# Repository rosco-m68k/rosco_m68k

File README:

# Motorola 68k single-board computer

This repository holds design files, firmware and software for my m68k 
single-board computer, AKA the Rosco_m68k.

You can find the project along with some logs about its development
on Hackaday: https://hackaday.io/project/164305-yet-another-m68k-homebrew

All released under the MIT licence. See LICENSE for details.

## Current design

Currently, the design for the system is:

* MC68010P10 at 8MHz, /DTACK grounded
* 16KB IO Space (0xF80000 - 0xFEFFFF)
* 16KB ROM (at 0xFC0000)
* 1MB RAM (0x0 - 0xFFFFF)
* TTL-based address decoding

In terms of software:

* Simple code in ROM to do various tests etc.
* Built with GCC and VASM

## Next steps

* Integrate MC68901 MFP
** This will provide timers, and a UART we can use to hook up a terminal. It also has some GPIOs and does interrupt handling (I already have the IC).
* Graphics - I'm thinking maybe Yamaha V9958 (assuming I can get hold of one)
** I would have liked to have used a Denise, but that would probably also require a (non-breadboard-friendly) Agnus.
** The datasheet and manual for the Denise probably aren't as easy to come by or complete, so there'd be more reverse-engineering.
* OS - Once the timers are available and I have some I/O capability, I want to build out the OS.
** Microkernel architecture (Similar in principle to Exec)
** Preemptive multitasking
** External storage (probably CF or SD in the first instance, though SD would require level shifting).

## Ideas for future enhancement

### Minimal memory protection

Extend address decoder to disallow access to certain locations based on 68k function pins.
E.g. in user mode:

	* Disallow ROM
	* Disallow IO
	* Disallow xKB at bottom of RAM (ExVecs and kernel heap)

The last one would make null dereferences generate a bus error.

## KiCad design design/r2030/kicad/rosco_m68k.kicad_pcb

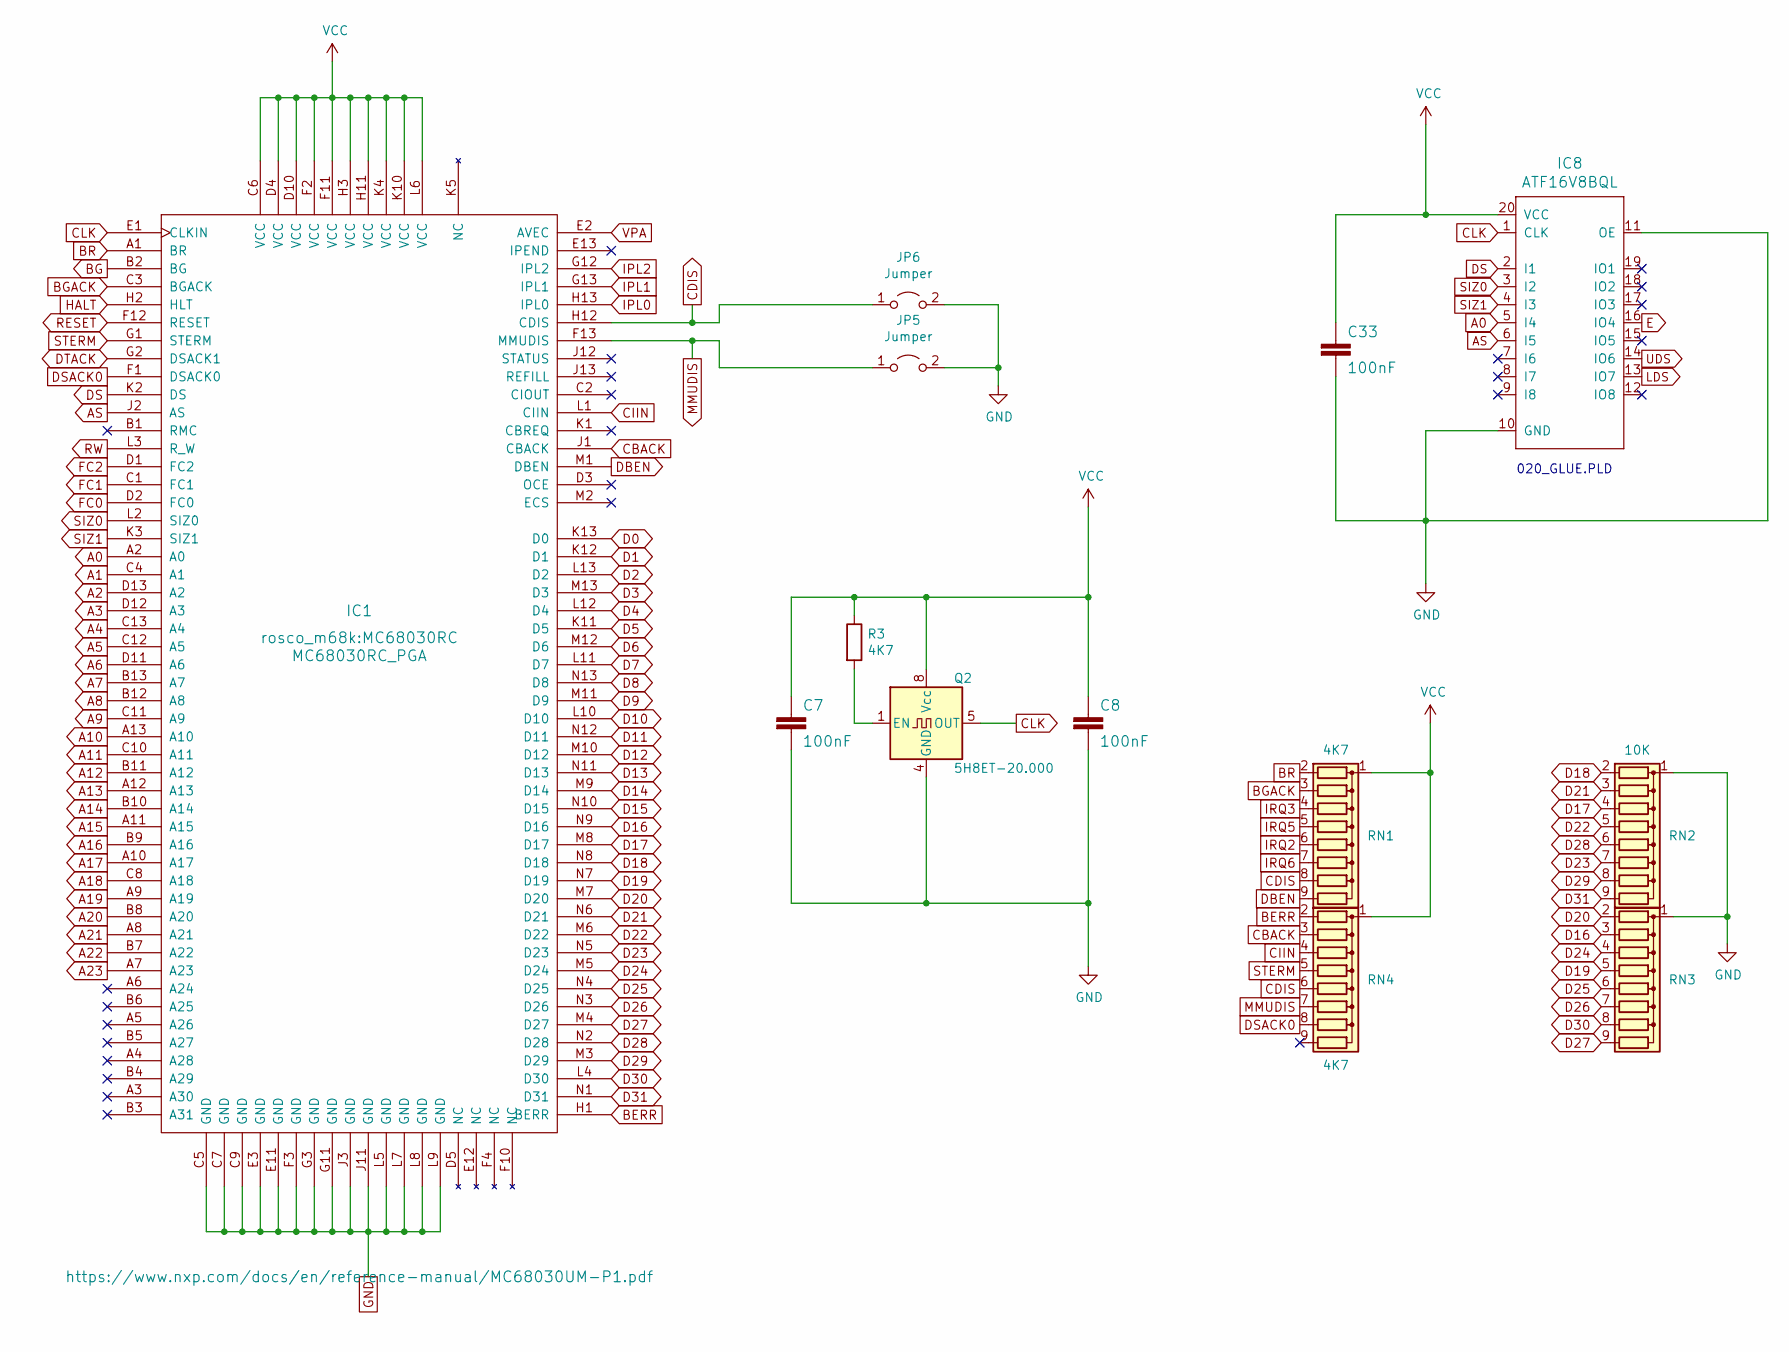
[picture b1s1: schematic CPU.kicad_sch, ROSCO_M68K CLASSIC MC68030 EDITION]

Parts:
C7, C8, C33: 100nF; C2.5-3
IC1: MC68030RC_PGA; MC68030RC
IC8: ATF16V8BQL; DIL20
JP5, JP6: Jumper; 1X02
Q2: 5H8ET-20.000; Oscillator_DIP-8
R3: 4K7; 0207_10
RN1, RN4: 4K7; R_Array_SIP9
RN2: 10K; R_Array_SIP9
RN3: R_Network08; R_Array_SIP9

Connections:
A0: IC1.A2 (A0), IC8.5 (I4)
A1: IC1.C4 (A1); also elsewhere on the board
A2: IC1.D13 (A2); also elsewhere on the board
A3: IC1.D12 (A3); also elsewhere on the board
A4: IC1.C13 (A4); also elsewhere on the board
A5: IC1.C12 (A5); also elsewhere on the board
A6: IC1.D11 (A6); also elsewhere on the board
A7: IC1.B13 (A7); also elsewhere on the board
A8: IC1.B12 (A8); also elsewhere on the board
A9: IC1.C11 (A9); also elsewhere on the board
A10: IC1.A13 (A10); also elsewhere on the board
A11: IC1.C10 (A11); also elsewhere on the board
A12: IC1.B11 (A12); also elsewhere on the board
A13: IC1.A12 (A13); also elsewhere on the board
A14: IC1.B10 (A14); also elsewhere on the board
A15: IC1.A11 (A15); also elsewhere on the board
A16: IC1.B9 (A16); also elsewhere on the board
A17: IC1.A10 (A17); also elsewhere on the board
A18: IC1.C8 (A18); also elsewhere on the board
A19: IC1.A9 (A19); also elsewhere on the board
A20: IC1.B8 (A20); also elsewhere on the board
A21: IC1.A8 (A21); also elsewhere on the board
A22: IC1.B7 (A22); also elsewhere on the board
A23: IC1.A7 (A23); also elsewhere on the board
AS: IC1.J2 (AS), IC8.6 (I5); also elsewhere on the board
BERR: IC1.H1 (BERR), RN4.2 (R1); also elsewhere on the board
BG: IC1.B2 (BG); also elsewhere on the board
BGACK: IC1.C3 (BGACK), RN1.3 (R2); also elsewhere on the board
BR: IC1.A1 (BR), RN1.2 (R1); also elsewhere on the board
CBACK: IC1.J1 (CBACK), RN4.3 (R2)
CDIS: IC1.H12 (CDIS), JP6.1 (A), RN1.8 (R7), RN4.6 (R5)
CIIN: IC1.L1 (CIIN), RN4.4 (R3)
CLK: IC1.E1 (CLKIN), IC8.1 (CLK), Q2.5 (OUT); also elsewhere on the board
D0: IC1.K13 (D0); also elsewhere on the board
D1: IC1.K12 (D1); also elsewhere on the board
D2: IC1.L13 (D2); also elsewhere on the board
D3: IC1.M13 (D3); also elsewhere on the board
D4: IC1.L12 (D4); also elsewhere on the board
D5: IC1.K11 (D5); also elsewhere on the board
D6: IC1.M12 (D6); also elsewhere on the board
D7: IC1.L11 (D7); also elsewhere on the board
D8: IC1.N13 (D8); also elsewhere on the board
D9: IC1.M11 (D9); also elsewhere on the board
D10: IC1.L10 (D10); also elsewhere on the board
D11: IC1.N12 (D11); also elsewhere on the board
D12: IC1.M10 (D12); also elsewhere on the board
D13: IC1.N11 (D13); also elsewhere on the board
D14: IC1.M9 (D14); also elsewhere on the board
D15: IC1.N10 (D15); also elsewhere on the board
D16: IC1.N9 (D16), RN3.3 (R2)
D17: IC1.M8 (D17), RN2.4 (R3)
D18: IC1.N8 (D18), RN2.2 (R1)
D19: IC1.N7 (D19), RN3.5 (R4)
D20: IC1.M7 (D20), RN3.2 (R1)
D21: IC1.N6 (D21), RN2.3 (R2)
D22: IC1.M6 (D22), RN2.5 (R4)
D23: IC1.N5 (D23), RN2.7 (R6)
D24: IC1.M5 (D24), RN3.4 (R3)
D25: IC1.N4 (D25), RN3.6 (R5)
D26: IC1.N3 (D26), RN3.7 (R6)
D27: IC1.M4 (D27), RN3.9 (R8)
D28: IC1.N2 (D28), RN2.6 (R5)
D29: IC1.M3 (D29), RN2.8 (R7)
D30: IC1.L4 (D30), RN3.8 (R7)
D31: IC1.N1 (D31), RN2.9 (R8)
DBEN: IC1.M1 (DBEN), RN1.9 (R8)
DS: IC1.K2 (DS), IC8.2 (I1)
DSACK0: IC1.F1 (DSACK0), RN4.8 (R7)
DTACK: IC1.G2 (DSACK1); also elsewhere on the board
E: IC8.16 (IO4); also elsewhere on the board
FC0: IC1.D2 (FC0); also elsewhere on the board
FC1: IC1.C1 (FC1); also elsewhere on the board
FC2: IC1.D1 (FC2); also elsewhere on the board
GND: C7.2, C8.2, C33.2, IC1.C5 (GND), IC1.C7 (GND), IC1.C9 (GND), IC1.E3 (GND), IC1.E11 (GND), IC1.F3 (GND), IC1.G3 (GND), IC1.G11 (GND), IC1.J3 (GND), IC1.J11 (GND), IC1.L5 (GND), IC1.L7 (GND), IC1.L8 (GND), IC1.L9 (GND), IC8.10 (GND), IC8.11 (OE), JP5.2 (B), JP6.2 (B), Q2.4 (GND), RN2.1 (common), RN3.1 (common); also elsewhere on the board
HALT: IC1.H2 (HLT); also elsewhere on the board
IPL0: IC1.H13 (IPL0); also elsewhere on the board
IPL1: IC1.G13 (IPL1); also elsewhere on the board
IPL2: IC1.G12 (IPL2); also elsewhere on the board
IRQ2: RN1.6 (R5); also elsewhere on the board
IRQ3: RN1.4 (R3); also elsewhere on the board
IRQ5: RN1.5 (R4); also elsewhere on the board
IRQ6: RN1.7 (R6); also elsewhere on the board
LDS: IC8.13 (IO7); also elsewhere on the board
MMUDIS: IC1.F13 (MMUDIS), JP5.1 (A), RN4.7 (R6)
unnamed: Q2.1 (EN), R3.2
RESET: IC1.F12 (RESET); also elsewhere on the board
RW: IC1.L3 (R_W); also elsewhere on the board
SIZ0: IC1.L2 (SIZ0), IC8.3 (I2)
SIZ1: IC1.K3 (SIZ1), IC8.4 (I3)
STERM: IC1.G1 (STERM), RN4.5 (R4)
UDS: IC8.14 (IO6); also elsewhere on the board
VCC: C7.1, C8.1, C33.1, IC1.C6 (VCC), IC1.D4 (VCC), IC1.D10 (VCC), IC1.F2 (VCC), IC1.F11 (VCC), IC1.H3 (VCC), IC1.H11 (VCC), IC1.K4 (VCC), IC1.K10 (VCC), IC1.L6 (VCC), IC8.20 (VCC), Q2.8 (Vcc), R3.1, RN1.1 (common), RN4.1 (common); also elsewhere on the board
VPA: IC1.E2 (AVEC); also elsewhere on the board

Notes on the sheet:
020_GLUE.PLD

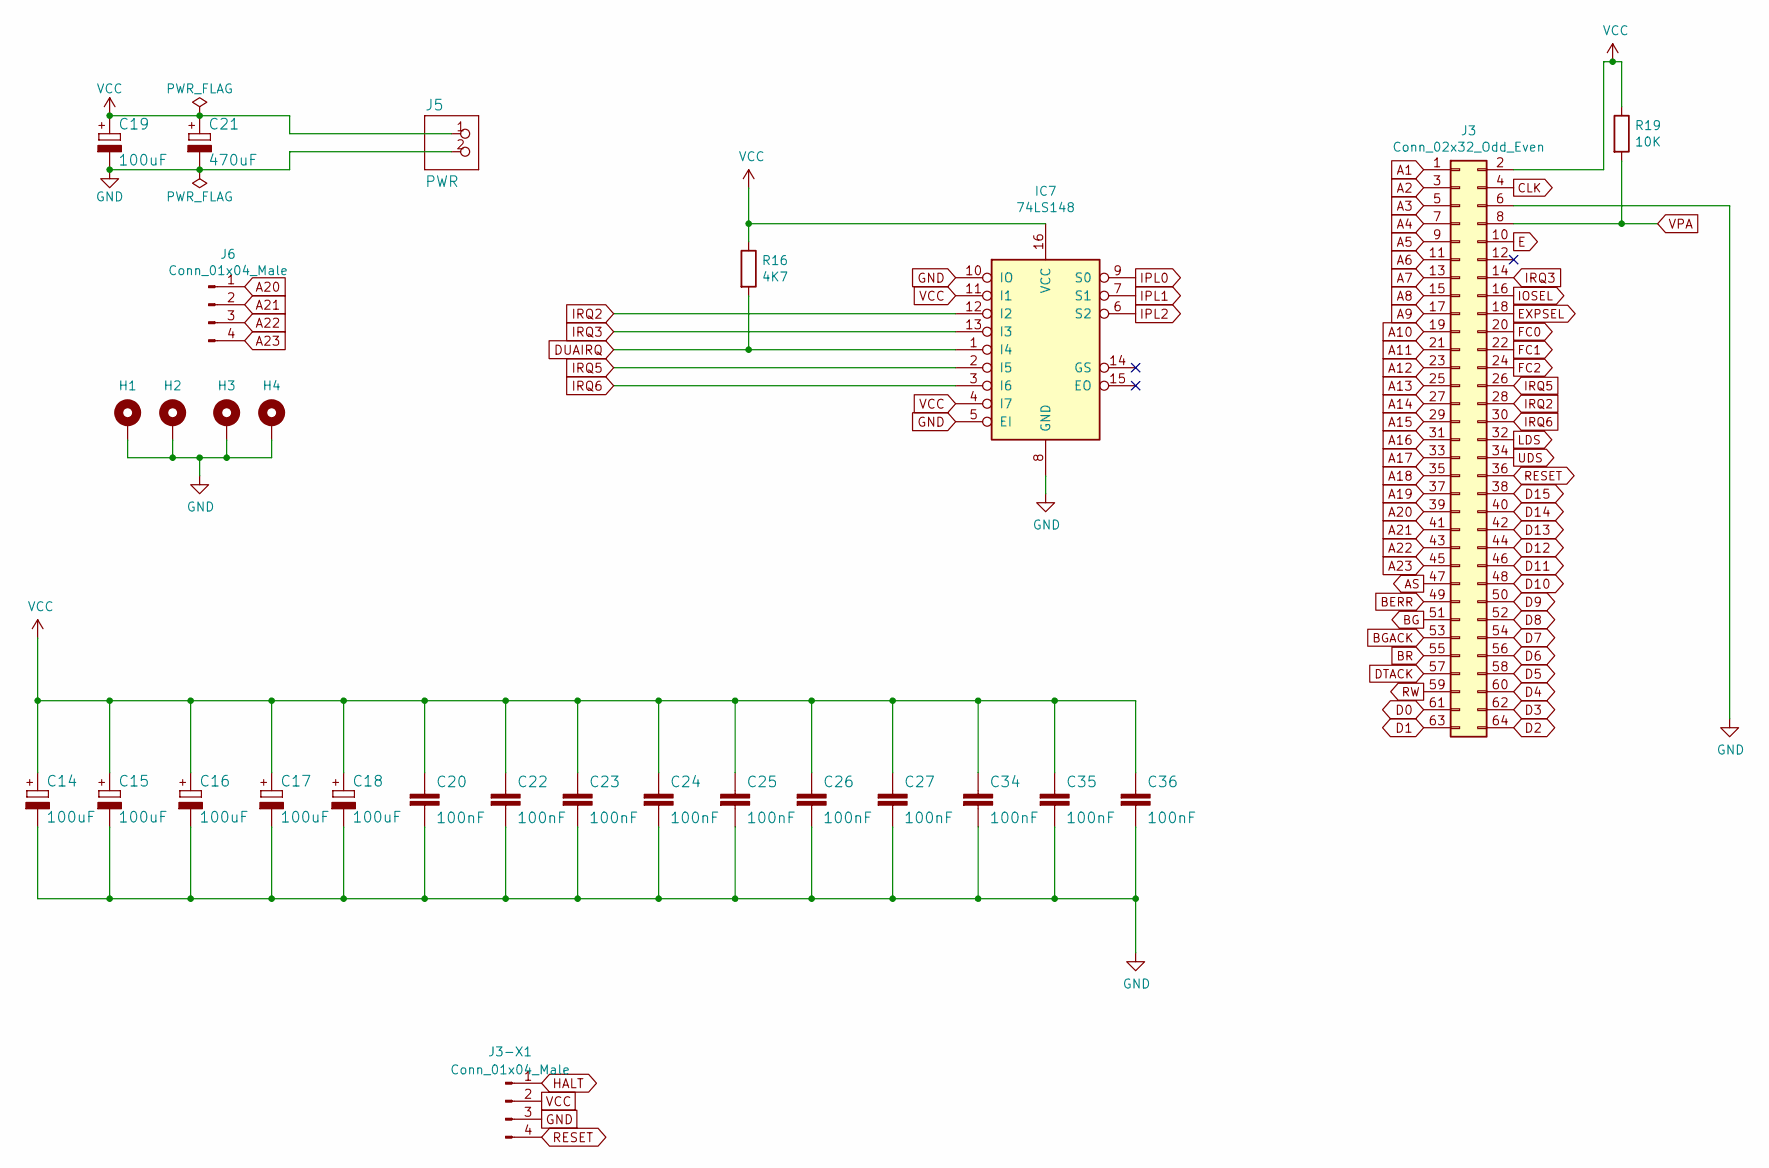
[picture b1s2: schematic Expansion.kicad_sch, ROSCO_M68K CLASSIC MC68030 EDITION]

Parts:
C14, C15, C16, C17, C18, C19: 100uF; E2,5-5
C20, C22, C23, C24, C25, C26, C27, C34, C35, C36: 100nF; C2.5-3
C21: 470uF; E3,5-10
H1, H2, H3, H4: MountingHole; MountingHole_3.2mm_M3_Pad
IC7: 74LS148; DIP-16_W7.62mm_LongPads
J3: Conn_02x32_Odd_Even; PinHeader_2x32_P2.54mm_Vertical
J3-X1, J6: Conn_01x04_Male; PinHeader_1x04_P2.54mm_Vertical
J5: PWR; 1X02
R16: 4K7; 0207_10
R19: 10K; 0207_10

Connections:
A1: J3.1; also elsewhere on the board
A2: J3.3; also elsewhere on the board
A3: J3.5; also elsewhere on the board
A4: J3.7; also elsewhere on the board
A5: J3.9; also elsewhere on the board
A6: J3.11; also elsewhere on the board
A7: J3.13; also elsewhere on the board
A8: J3.15; also elsewhere on the board
A9: J3.17; also elsewhere on the board
A10: J3.19; also elsewhere on the board
A11: J3.21; also elsewhere on the board
A12: J3.23; also elsewhere on the board
A13: J3.25; also elsewhere on the board
A14: J3.27; also elsewhere on the board
A15: J3.29; also elsewhere on the board
A16: J3.31; also elsewhere on the board
A17: J3.33; also elsewhere on the board
A18: J3.35; also elsewhere on the board
A19: J3.37; also elsewhere on the board
A20: J3.39, J6.1; also elsewhere on the board
A21: J3.41, J6.2; also elsewhere on the board
A22: J3.43, J6.3; also elsewhere on the board
A23: J3.45, J6.4; also elsewhere on the board
AS: J3.47; also elsewhere on the board
BERR: J3.49; also elsewhere on the board
BG: J3.51; also elsewhere on the board
BGACK: J3.53; also elsewhere on the board
BR: J3.55; also elsewhere on the board
CLK: J3.4; also elsewhere on the board
D0: J3.61; also elsewhere on the board
D1: J3.63; also elsewhere on the board
D2: J3.64; also elsewhere on the board
D3: J3.62; also elsewhere on the board
D4: J3.60; also elsewhere on the board
D5: J3.58; also elsewhere on the board
D6: J3.56; also elsewhere on the board
D7: J3.54; also elsewhere on the board
D8: J3.52; also elsewhere on the board
D9: J3.50; also elsewhere on the board
D10: J3.48; also elsewhere on the board
D11: J3.46; also elsewhere on the board
D12: J3.44; also elsewhere on the board
D13: J3.42; also elsewhere on the board
D14: J3.40; also elsewhere on the board
D15: J3.38; also elsewhere on the board
DTACK: J3.57; also elsewhere on the board
DUAIRQ: IC7.1 (I4), R16.2; also elsewhere on the board
E: J3.10; also elsewhere on the board
EXPSEL: J3.18; also elsewhere on the board
FC0: J3.20; also elsewhere on the board
FC1: J3.22; also elsewhere on the board
FC2: J3.24; also elsewhere on the board
GND: C14.-, C15.-, C16.-, C17.-, C18.-, C19.-, C20.2, C21.-, C22.2, C23.2, C24.2, C25.2, C26.2, C27.2, C34.2, C35.2, C36.2, H1.1, H2.1, H3.1, H4.1, IC7.5 (EI), IC7.8 (GND), IC7.10 (IO), J3.6, J3-X1.3, J5.2; also elsewhere on the board
HALT: J3-X1.1; also elsewhere on the board
IOSEL: J3.16; also elsewhere on the board
IPL0: IC7.9 (S0); also elsewhere on the board
IPL1: IC7.7 (S1); also elsewhere on the board
IPL2: IC7.6 (S2); also elsewhere on the board
IRQ2: IC7.12 (I2), J3.28; also elsewhere on the board
IRQ3: IC7.13 (I3), J3.14; also elsewhere on the board
IRQ5: IC7.2 (I5), J3.26; also elsewhere on the board
IRQ6: IC7.3 (I6), J3.30; also elsewhere on the board
LDS: J3.32; also elsewhere on the board
RESET: J3.36, J3-X1.4; also elsewhere on the board
RW: J3.59; also elsewhere on the board
UDS: J3.34; also elsewhere on the board
VCC: C14.+, C15.+, C16.+, C17.+, C18.+, C19.+, C20.1, C21.+, C22.1, C23.1, C24.1, C25.1, C26.1, C27.1, C34.1, C35.1, C36.1, IC7.4 (I7), IC7.11 (I1), IC7.16 (VCC), J3.2, J3-X1.2, J5.1, R16.1, R19.1; also elsewhere on the board
VPA: J3.8, R19.2; also elsewhere on the board

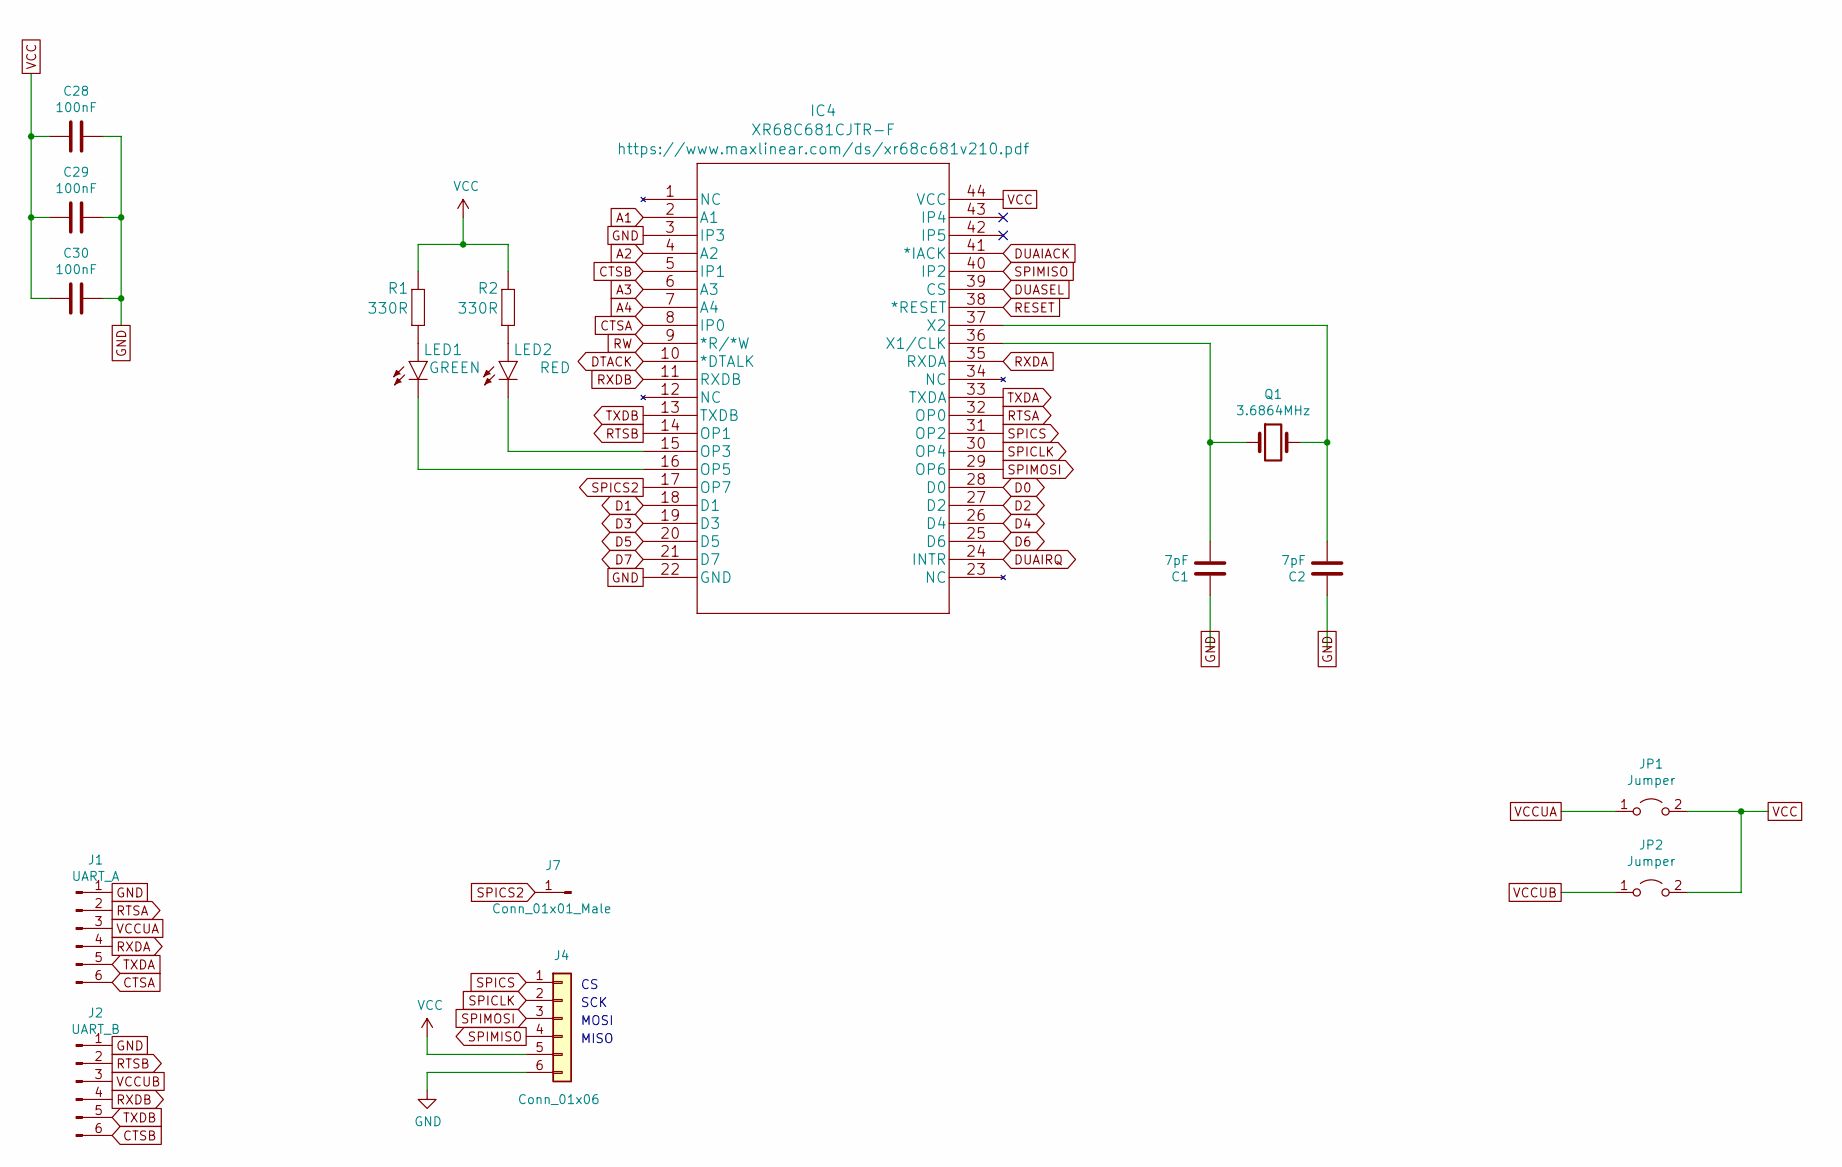
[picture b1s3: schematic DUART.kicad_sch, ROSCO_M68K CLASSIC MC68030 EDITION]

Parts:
C1, C2: 7pF; C2.5_or_3.5-3
C28, C29, C30: 100nF; C2.5-3
IC4: XR68C681CJTR-F; PLCC-44_THT-Socket
J1: UART_A; 1X06
J2: UART_B; 1X06
J4: Conn_01x06; 1X06
J7: Conn_01x01_Male; PinHeader_1x01_P2.54mm_Vertical
JP1, JP2: Jumper; 1X02
LED1: GREEN; LED5MM
LED2: RED; LED5MM
Q1: 3.6864MHz; Crystal_HC49-4H_Vertical
R1, R2: 330R; 0207_10

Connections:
A1: IC4.2 (A1); also elsewhere on the board
A2: IC4.4 (A2); also elsewhere on the board
A3: IC4.6 (A3); also elsewhere on the board
A4: IC4.7 (A4); also elsewhere on the board
CTSA: IC4.8 (IP0), J1.6
CTSB: IC4.5 (IP1), J2.6
D0: IC4.28 (D0); also elsewhere on the board
D1: IC4.18 (D1); also elsewhere on the board
D2: IC4.27 (D2); also elsewhere on the board
D3: IC4.19 (D3); also elsewhere on the board
D4: IC4.26 (D4); also elsewhere on the board
D5: IC4.20 (D5); also elsewhere on the board
D6: IC4.25 (D6); also elsewhere on the board
D7: IC4.21 (D7); also elsewhere on the board
DTACK: IC4.10 (*DTALK); also elsewhere on the board
DUAIACK: IC4.41 (*IACK); also elsewhere on the board
DUAIRQ: IC4.24 (INTR); also elsewhere on the board
DUASEL: IC4.39 (CS); also elsewhere on the board
GND: C1.1, C2.1, C28.1, C29.1, C30.1, IC4.3 (IP3), IC4.22 (GND), J1.1, J2.1, J4.6; also elsewhere on the board
unnamed: IC4.15 (OP3), LED2.K (C)
unnamed: IC4.16 (OP5), LED1.K (C)
unnamed: C1.2, IC4.36 (X1/CLK), Q1.1
unnamed: C2.2, IC4.37 (X2), Q1.2
unnamed: LED1.A, R1.1
unnamed: LED2.A, R2.1
RESET: IC4.38 (*RESET); also elsewhere on the board
RTSA: IC4.32 (OP0), J1.2
RTSB: IC4.14 (OP1), J2.2
RW: IC4.9 (*R/*W); also elsewhere on the board
RXDA: IC4.35 (RXDA), J1.4
RXDB: IC4.11 (RXDB), J2.4
SPICLK: IC4.30 (OP4), J4.2
SPICS: IC4.31 (OP2), J4.1
SPICS2: IC4.17 (OP7), J7.1
SPIMISO: IC4.40 (IP2), J4.4
SPIMOSI: IC4.29 (OP6), J4.3
TXDA: IC4.33 (TXDA), J1.5
TXDB: IC4.13 (TXDB), J2.5
VCC: C28.2, C29.2, C30.2, IC4.44 (VCC), J4.5, JP1.2 (B), JP2.2 (B), R1.2, R2.2; also elsewhere on the board
VCCUA: J1.3, JP1.1 (A)
VCCUB: J2.3, JP2.1 (A)

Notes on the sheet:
MISO
SCK
MOSI

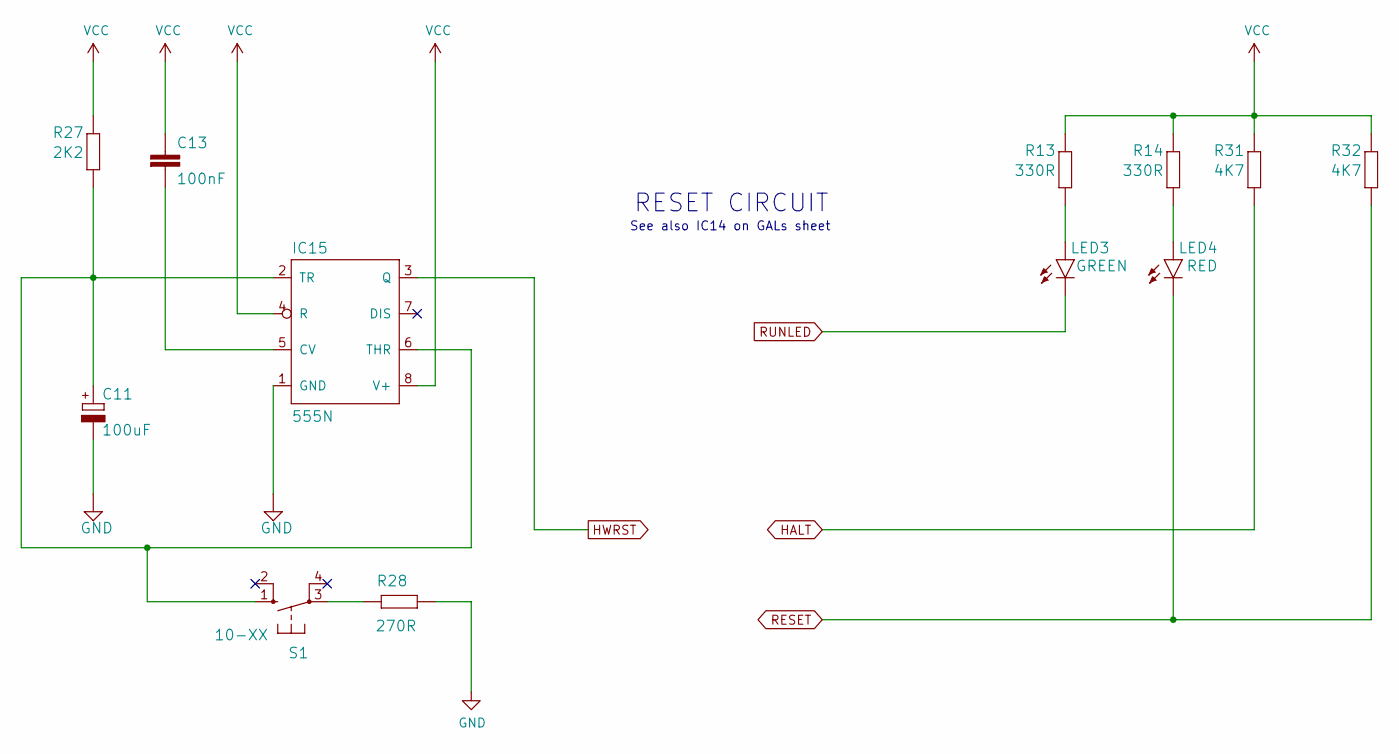
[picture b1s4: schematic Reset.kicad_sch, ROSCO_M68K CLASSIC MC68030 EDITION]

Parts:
C11: 100uF; E2,5-5
C13: 100nF; C2.5-3
IC15: 555N; DIP-8_W7.62mm_LongPads
LED3: GREEN; LED5MM
LED4: RED; LED5MM
R13, R14: 330R; 0207_10
R27: 2K2; 0207_10
R28: 270R; 0207_10
R31, R32: 4K7; 0207_10
S1: 10-XX; B3F-10XX

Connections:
GND: C11.-, IC15.1 (GND), R28.1; also elsewhere on the board
HALT: R31.1; also elsewhere on the board
HWRST: IC15.3 (Q); also elsewhere on the board
unnamed: C13.2, IC15.5 (CV)
unnamed: C11.+, IC15.2 (TR), IC15.6 (THR), R27.1, S1.1 (S)
unnamed: LED3.A, R13.1
unnamed: LED4.A, R14.1
unnamed: R28.2, S1.3
RESET: LED4.K (C), R32.1; also elsewhere on the board
RUNLED: LED3.K (C); also elsewhere on the board
VCC: C13.1, IC15.4 (R), IC15.8 (V+), R13.2, R14.2, R27.2, R31.2, R32.2; also elsewhere on the board

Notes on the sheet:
See also IC14 on GALs sheet
RESET CIRCUIT

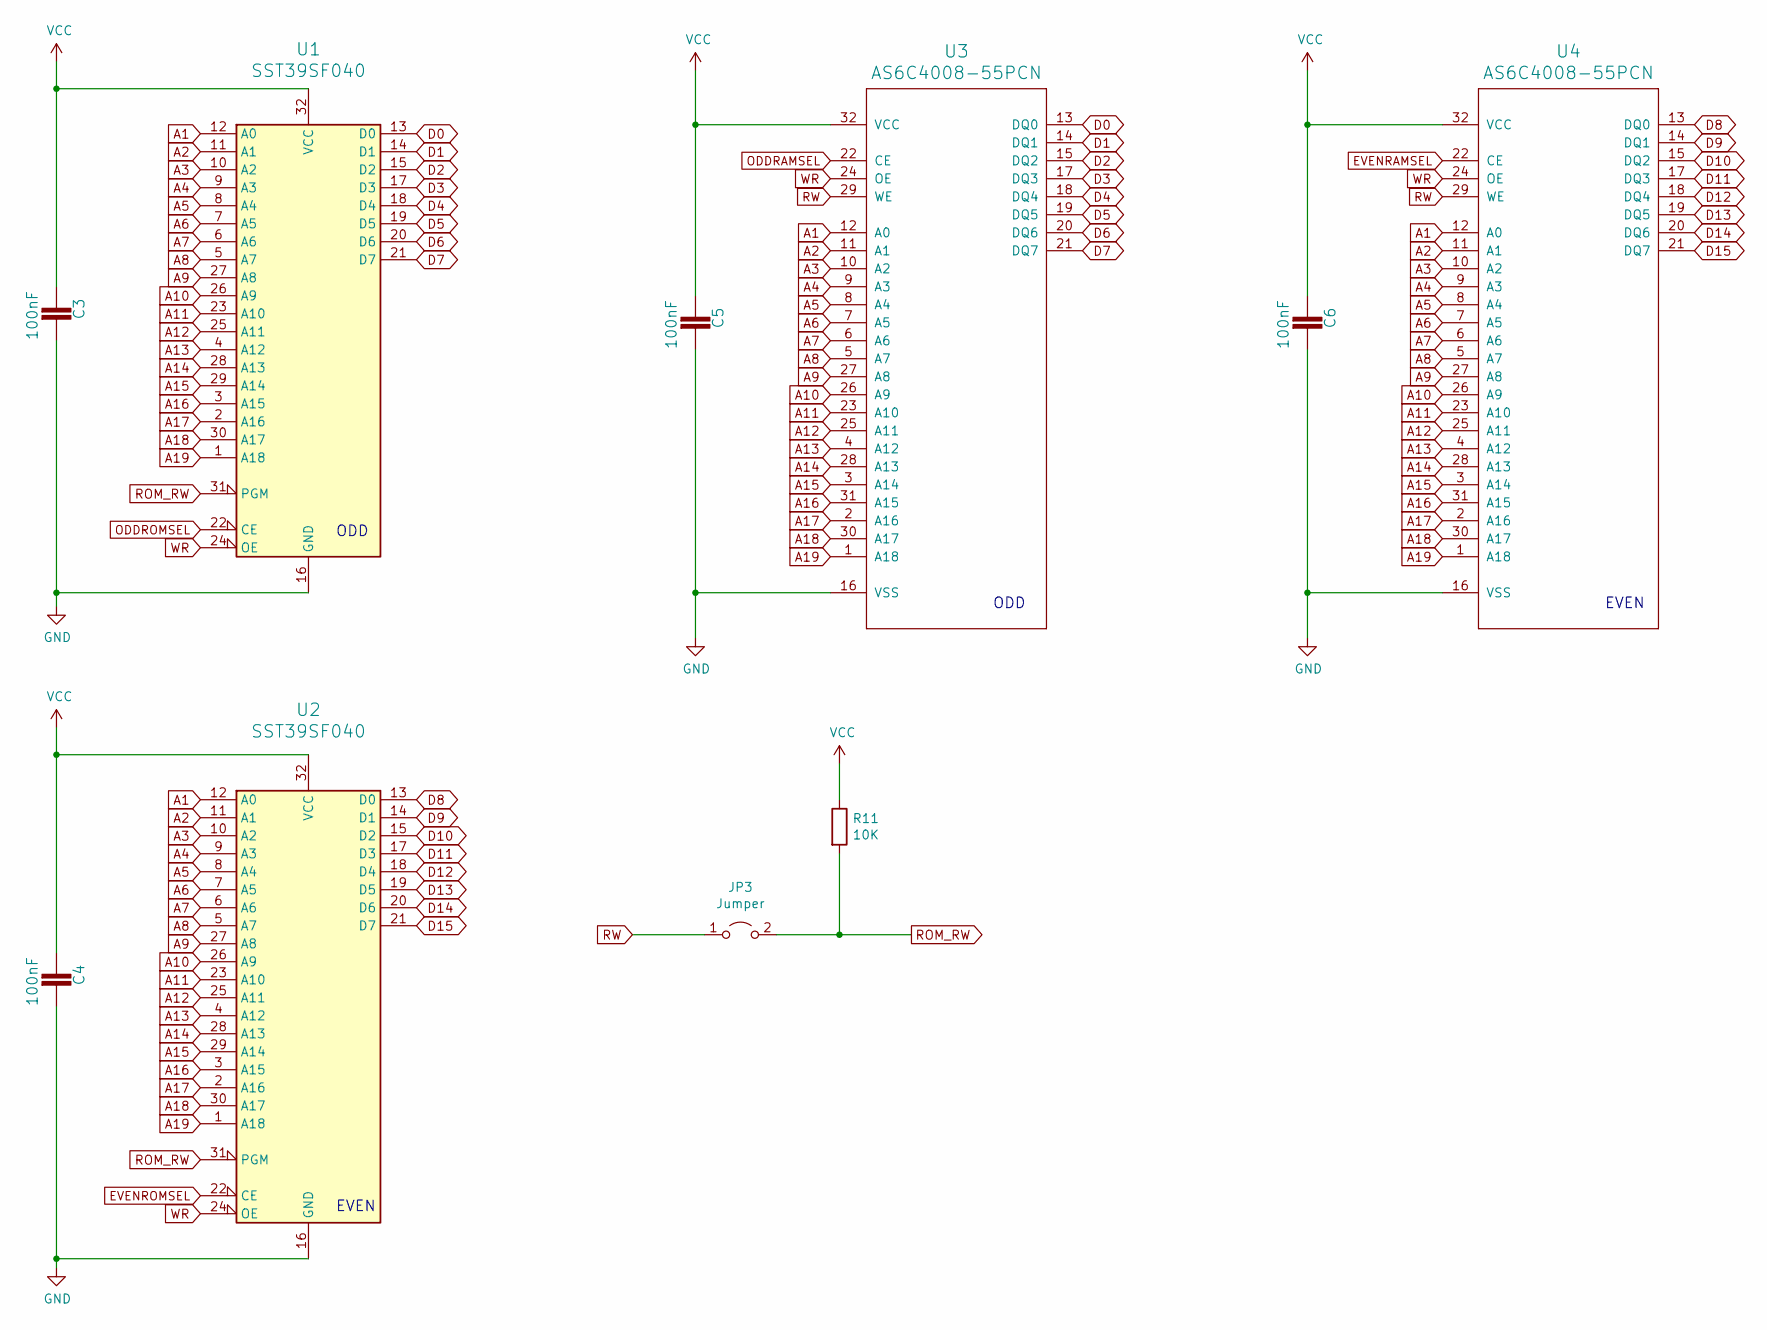
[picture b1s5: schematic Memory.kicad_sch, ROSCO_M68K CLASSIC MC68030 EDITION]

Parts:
C3, C4, C5, C6: 100nF; C2.5-3
JP3: Jumper; 1X02
R11: 10K; 0207_10
U1, U2: SST39SF040; DIP-32_W15.24mm_LongPads
U3, U4: AS6C4008-55PCN; DIP-32_W15.24mm_LongPads

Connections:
A1: U1.12 (A0), U2.12 (A0), U3.12 (A0), U4.12 (A0); also elsewhere on the board
A2: U1.11 (A1), U2.11 (A1), U3.11 (A1), U4.11 (A1); also elsewhere on the board
A3: U1.10 (A2), U2.10 (A2), U3.10 (A2), U4.10 (A2); also elsewhere on the board
A4: U1.9 (A3), U2.9 (A3), U3.9 (A3), U4.9 (A3); also elsewhere on the board
A5: U1.8 (A4), U2.8 (A4), U3.8 (A4), U4.8 (A4); also elsewhere on the board
A6: U1.7 (A5), U2.7 (A5), U3.7 (A5), U4.7 (A5); also elsewhere on the board
A7: U1.6 (A6), U2.6 (A6), U3.6 (A6), U4.6 (A6); also elsewhere on the board
A8: U1.5 (A7), U2.5 (A7), U3.5 (A7), U4.5 (A7); also elsewhere on the board
A9: U1.27 (A8), U2.27 (A8), U3.27 (A8), U4.27 (A8); also elsewhere on the board
A10: U1.26 (A9), U2.26 (A9), U3.26 (A9), U4.26 (A9); also elsewhere on the board
A11: U1.23 (A10), U2.23 (A10), U3.23 (A10), U4.23 (A10); also elsewhere on the board
A12: U1.25 (A11), U2.25 (A11), U3.25 (A11), U4.25 (A11); also elsewhere on the board
A13: U1.4 (A12), U2.4 (A12), U3.4 (A12), U4.4 (A12); also elsewhere on the board
A14: U1.28 (A13), U2.28 (A13), U3.28 (A13), U4.28 (A13); also elsewhere on the board
A15: U1.29 (A14), U2.29 (A14), U3.3 (A14), U4.3 (A14); also elsewhere on the board
A16: U1.3 (A15), U2.3 (A15), U3.31 (A15), U4.31 (A15); also elsewhere on the board
A17: U1.2 (A16), U2.2 (A16), U3.2 (A16), U4.2 (A16); also elsewhere on the board
A18: U1.30 (A17), U2.30 (A17), U3.30 (A17), U4.30 (A17); also elsewhere on the board
A19: U1.1 (A18), U2.1 (A18), U3.1 (A18), U4.1 (A18); also elsewhere on the board
D0: U1.13 (D0), U3.13 (DQ0); also elsewhere on the board
D1: U1.14 (D1), U3.14 (DQ1); also elsewhere on the board
D2: U1.15 (D2), U3.15 (DQ2); also elsewhere on the board
D3: U1.17 (D3), U3.17 (DQ3); also elsewhere on the board
D4: U1.18 (D4), U3.18 (DQ4); also elsewhere on the board
D5: U1.19 (D5), U3.19 (DQ5); also elsewhere on the board
D6: U1.20 (D6), U3.20 (DQ6); also elsewhere on the board
D7: U1.21 (D7), U3.21 (DQ7); also elsewhere on the board
D8: U2.13 (D0), U4.13 (DQ0); also elsewhere on the board
D9: U2.14 (D1), U4.14 (DQ1); also elsewhere on the board
D10: U2.15 (D2), U4.15 (DQ2); also elsewhere on the board
D11: U2.17 (D3), U4.17 (DQ3); also elsewhere on the board
D12: U2.18 (D4), U4.18 (DQ4); also elsewhere on the board
D13: U2.19 (D5), U4.19 (DQ5); also elsewhere on the board
D14: U2.20 (D6), U4.20 (DQ6); also elsewhere on the board
D15: U2.21 (D7), U4.21 (DQ7); also elsewhere on the board
EVENRAMSEL: U4.22 (CE); also elsewhere on the board
EVENROMSEL: U2.22 (CE); also elsewhere on the board
GND: C3.2, C4.2, C5.2, C6.2, U1.16 (GND), U2.16 (GND), U3.16 (VSS), U4.16 (VSS); also elsewhere on the board
ODDRAMSEL: U3.22 (CE); also elsewhere on the board
ODDROMSEL: U1.22 (CE); also elsewhere on the board
ROM_RW: JP3.2 (B), R11.2, U1.31 (PGM), U2.31 (PGM)
RW: JP3.1 (A), U3.29 (WE), U4.29 (WE); also elsewhere on the board
VCC: C3.1, C4.1, C5.1, C6.1, R11.1, U1.32 (VCC), U2.32 (VCC), U3.32 (VCC), U4.32 (VCC); also elsewhere on the board
WR: U1.24 (OE), U2.24 (OE), U3.24 (OE), U4.24 (OE); also elsewhere on the board

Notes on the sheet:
EVEN
ODD

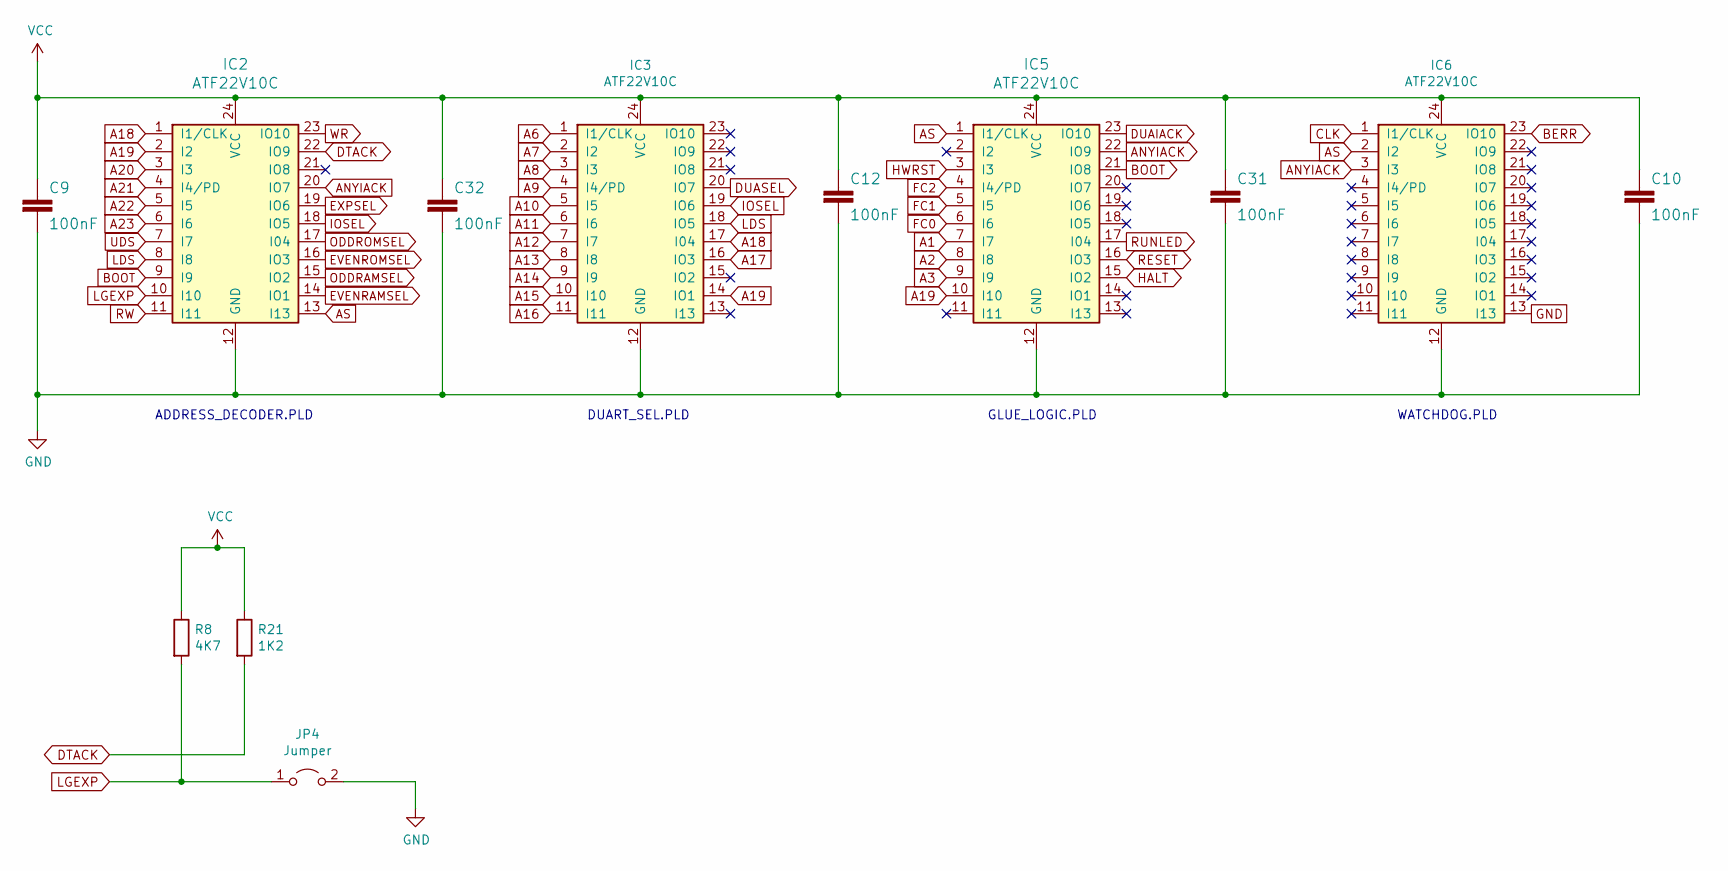
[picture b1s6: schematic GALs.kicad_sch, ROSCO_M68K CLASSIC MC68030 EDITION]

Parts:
C9, C10, C12, C31, C32: 100nF; C2.5-3
IC2, IC3, IC5, IC6: ATF22V10C; DIP-24_W7.62mm_Socket_LongPads
JP4: Jumper; 1X02
R8: 4K7; 0207_10
R21: 1K2; 0207_10

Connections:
A1: IC5.7 (I7); also elsewhere on the board
A2: IC5.8 (I8); also elsewhere on the board
A3: IC5.9 (I9); also elsewhere on the board
A6: IC3.1 (I1/CLK); also elsewhere on the board
A7: IC3.2 (I2); also elsewhere on the board
A8: IC3.3 (I3); also elsewhere on the board
A9: IC3.4 (I4/PD); also elsewhere on the board
A10: IC3.5 (I5); also elsewhere on the board
A11: IC3.6 (I6); also elsewhere on the board
A12: IC3.7 (I7); also elsewhere on the board
A13: IC3.8 (I8); also elsewhere on the board
A14: IC3.9 (I9); also elsewhere on the board
A15: IC3.10 (I10); also elsewhere on the board
A16: IC3.11 (I11); also elsewhere on the board
A17: IC3.16 (IO3); also elsewhere on the board
A18: IC2.1 (I1/CLK), IC3.17 (I04); also elsewhere on the board
A19: IC2.2 (I2), IC3.14 (IO1), IC5.10 (I10); also elsewhere on the board
A20: IC2.3 (I3); also elsewhere on the board
A21: IC2.4 (I4/PD); also elsewhere on the board
A22: IC2.5 (I5); also elsewhere on the board
A23: IC2.6 (I6); also elsewhere on the board
ANYIACK: IC2.20 (IO7), IC5.22 (IO9), IC6.3 (I3)
AS: IC2.13 (I13), IC5.1 (I1/CLK), IC6.2 (I2); also elsewhere on the board
BERR: IC6.23 (IO10); also elsewhere on the board
BOOT: IC2.9 (I9), IC5.21 (IO8)
CLK: IC6.1 (I1/CLK); also elsewhere on the board
DTACK: IC2.22 (IO9), R21.2; also elsewhere on the board
DUAIACK: IC5.23 (IO10); also elsewhere on the board
DUASEL: IC3.20 (IO7); also elsewhere on the board
EVENRAMSEL: IC2.14 (IO1); also elsewhere on the board
EVENROMSEL: IC2.16 (IO3); also elsewhere on the board
EXPSEL: IC2.19 (IO6); also elsewhere on the board
FC0: IC5.6 (I6); also elsewhere on the board
FC1: IC5.5 (I5); also elsewhere on the board
FC2: IC5.4 (I4/PD); also elsewhere on the board
GND: C9.2, C10.2, C12.2, C31.2, C32.2, IC2.12 (GND), IC3.12 (GND), IC5.12 (GND), IC6.12 (GND), IC6.13 (I13), JP4.2 (B); also elsewhere on the board
HALT: IC5.15 (IO2); also elsewhere on the board
HWRST: IC5.3 (I3); also elsewhere on the board
IOSEL: IC2.18 (IO5), IC3.19 (IO6); also elsewhere on the board
LDS: IC2.8 (I8), IC3.18 (IO5); also elsewhere on the board
LGEXP: IC2.10 (I10), JP4.1 (A), R8.2
ODDRAMSEL: IC2.15 (IO2); also elsewhere on the board
ODDROMSEL: IC2.17 (I04); also elsewhere on the board
RESET: IC5.16 (IO3); also elsewhere on the board
RUNLED: IC5.17 (I04); also elsewhere on the board
RW: IC2.11 (I11); also elsewhere on the board
UDS: IC2.7 (I7); also elsewhere on the board
VCC: C9.1, C10.1, C12.1, C31.1, C32.1, IC2.24 (VCC), IC3.24 (VCC), IC5.24 (VCC), IC6.24 (VCC), R8.1, R21.1; also elsewhere on the board
WR: IC2.23 (IO10); also elsewhere on the board

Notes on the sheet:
GLUE_LOGIC.PLD
ADDRESS_DECODER.PLD
DUART_SEL.PLD
WATCHDOG.PLD

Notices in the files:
design/r1.2/kicad/Cpu_Ram_Rom.sch:
Copyright 2019-2020 Ross Bamford and Contributors
design/r1.2/kicad/Expansion.sch:
Copyright 2019-2021 Ross Bamford and Contributors
design/r1.2/kicad/rosco_m68k.kicad_pcb:
Copyright ©2021
design/r1/kicad/rosco_m68k.kicad_pcb:
copyright 2020
design/r2/kicad/CPU.kicad_sch:
Copyright 2019-2022 Ross Bamford and Contributors
design/r2/kicad/rosco_m68k.kicad_pcb:
Copyright ©2019-2021 Ross Bamford & Contributors
Copyright ©2019-2022
design/r2030/kicad/CPU.kicad_sch:
Copyright 2019-2023 Ross Bamford and Contributors
